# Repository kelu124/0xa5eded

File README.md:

# An 8-bit, 100Msps ADC standalone pHAT

aka 0xA5EDED == sha1(pHATrick)

# Description

An 8-bit, 125Msps ADC standalone pHAT

More? @TODO

# What

__Beware - these need to be updated with actual assembled board. v2 includes sees top going bottom and vice versa.__

# Acquisition of a square/sine wave

Signal coming out of a cheap DSO, should be around square, 4MHz

### Acquisition 

### Spectrum of a square wave at 125Msps

# Changes from v1

* Remove i2c to something simpler - MCP40D17T
* Let user choose offset or not
* Check OPAMP capa to get a 60MHz cutoff
* BAV / MD0100 to be removed
* Putting the rp2040 under the board, to expose the beautiful art to users

# License

This work is based a previous TAPR exploration, the [pic0rick project](https://github.com/kelu124/pic0rick/) - these open hardware and software, developped with open-source elements as much as possible.

Copyright Luc Jonveaux (kelu124@gmail.com) 2024

* The hardware is licensed under TAPR Open Hardware License (www.tapr.org/OHL)
* The software components are free software: you can redistribute it and/or modify it under the terms of the GNU General Public License as published by the Free Software Foundation, either version 3 of the License, or (at your option) any later version.
* The documentation is licensed under a [Creative Commons Attribution-ShareAlike 3.0 Unported License](http://creativecommons.org/licenses/by-sa/3.0/).

## Disclaimer

This project is distributed WITHOUT ANY EXPRESS OR IMPLIED WARRANTY, INCLUDING OF MERCHANTABILITY, SATISFACTORY QUALITY AND FITNESS FOR A PARTICULAR PURPOSE.

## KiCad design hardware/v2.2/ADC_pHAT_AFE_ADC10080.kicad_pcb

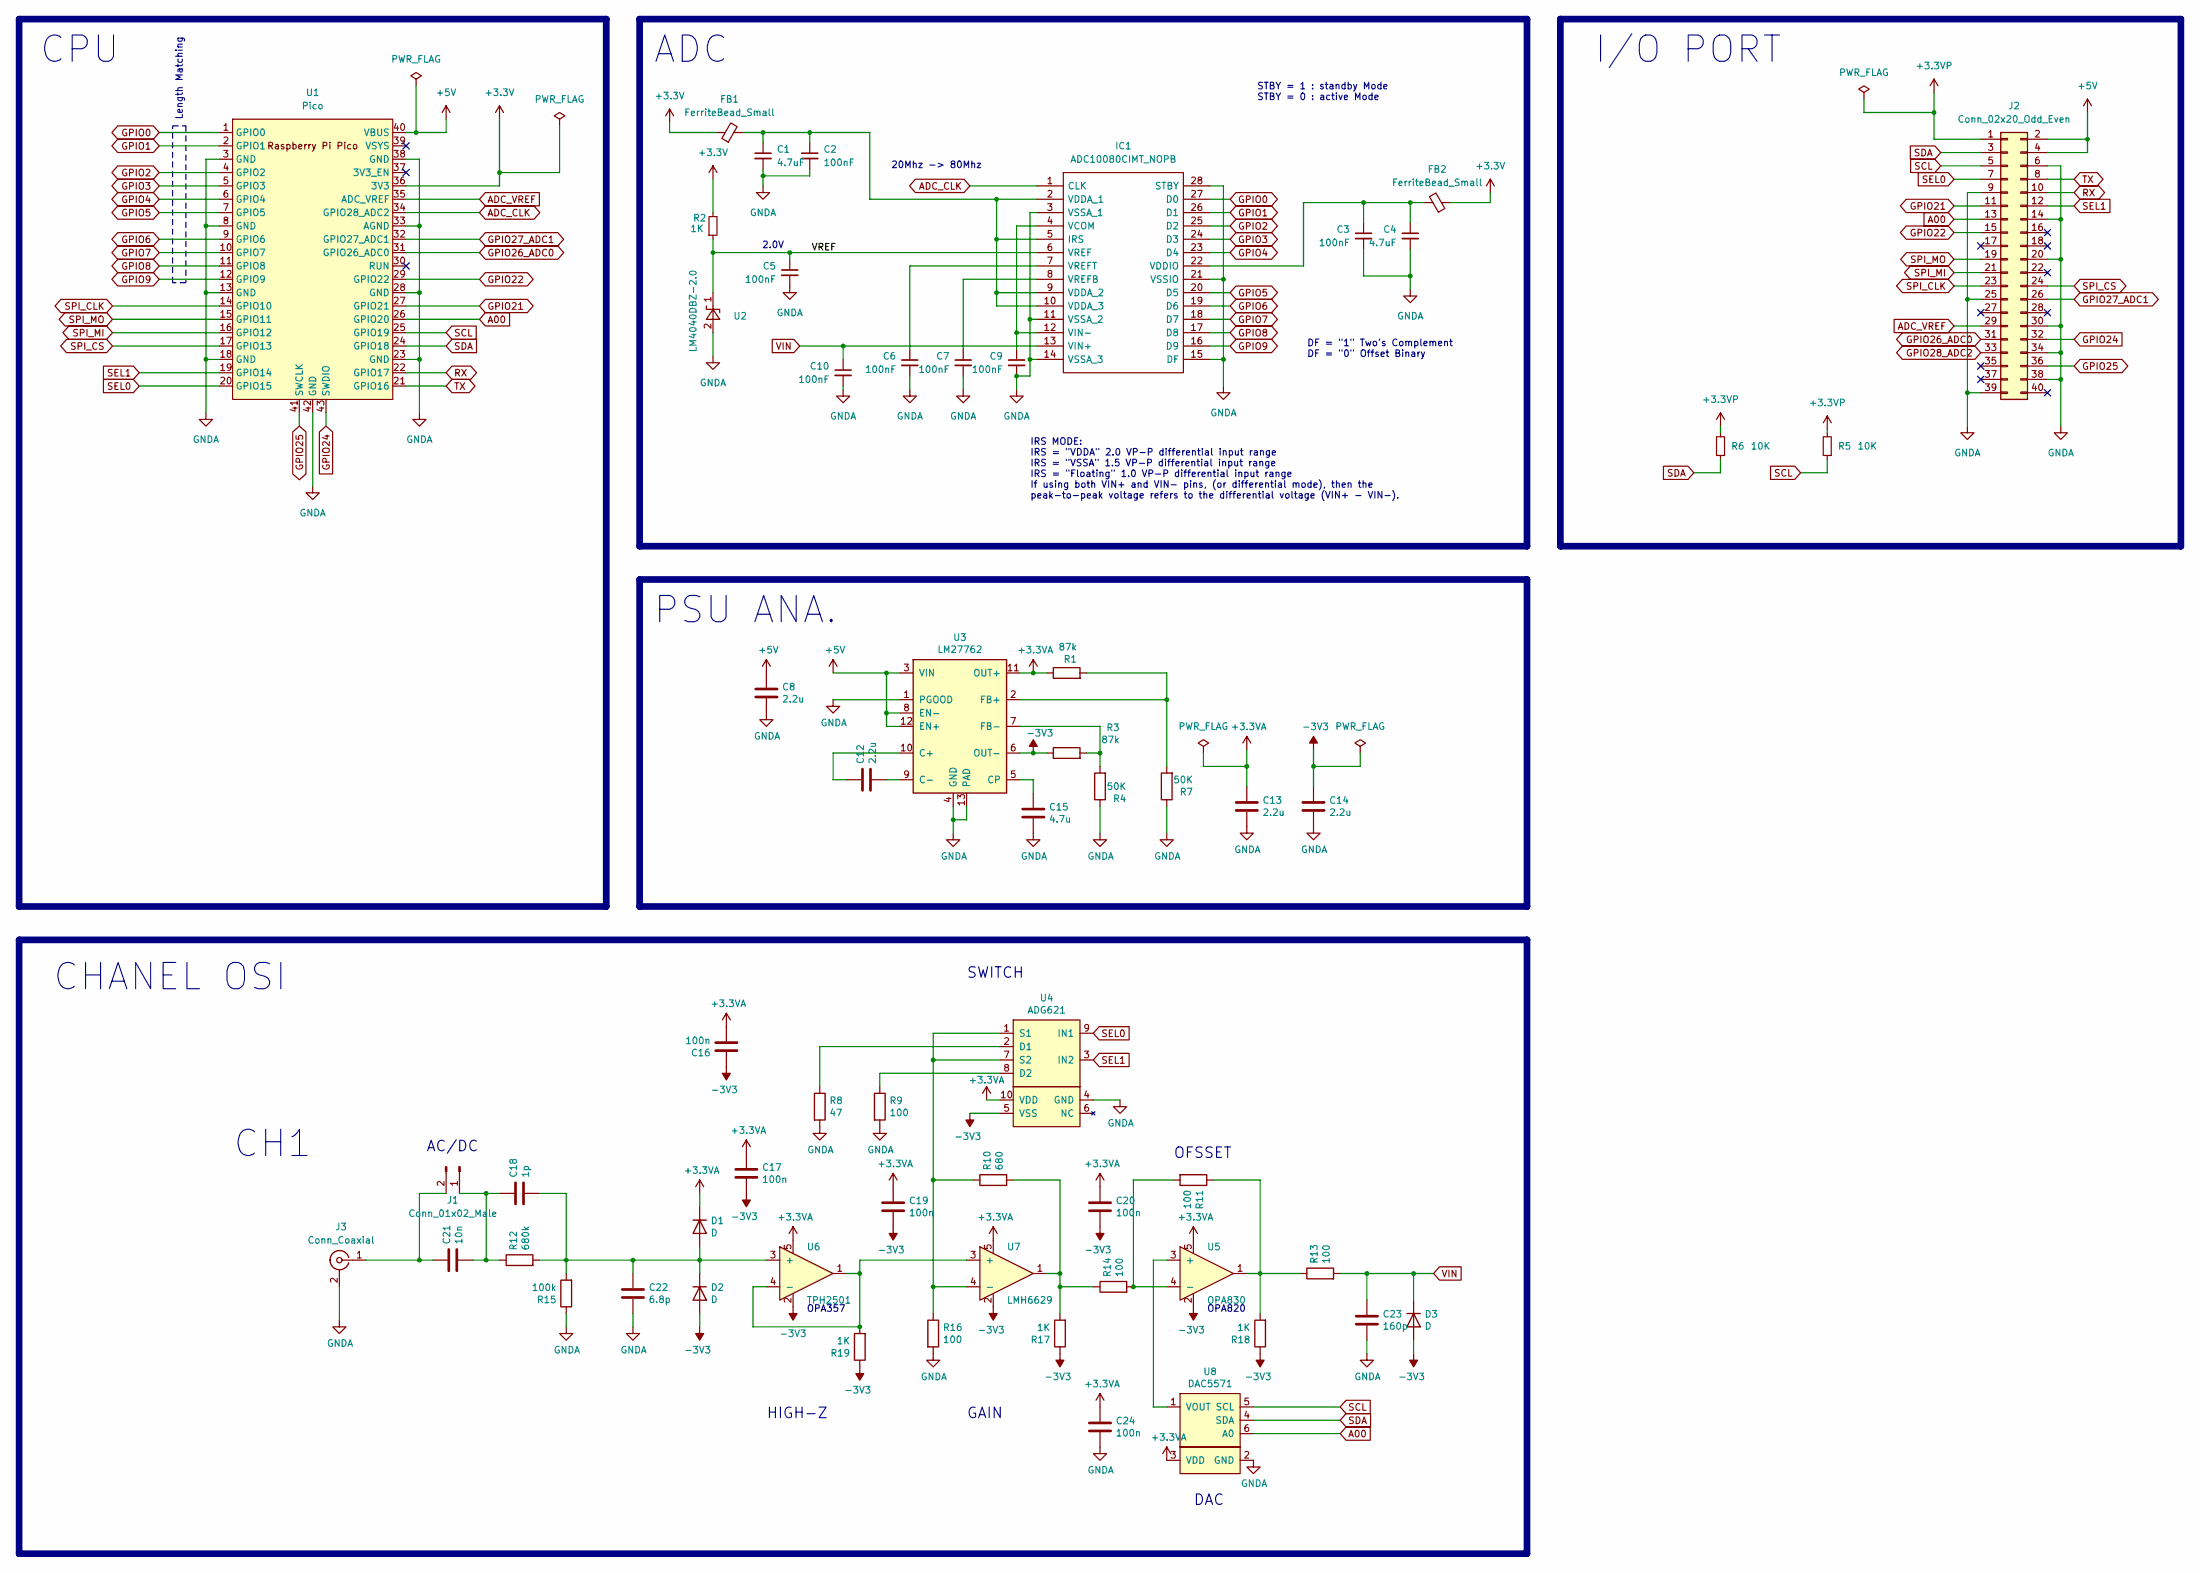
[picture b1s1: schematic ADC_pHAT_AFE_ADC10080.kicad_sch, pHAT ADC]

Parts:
C1, C4: 4.7uF; R_0603_1608Metric
C2, C3, C5, C6, C7, C9, C10: 100nF; R_0603_1608Metric
C8, C12, C13, C14: 2.2u; C_0603_1608Metric; MFR. Part # CL10A225KO8NNNC; LCSC Part # C23630
C15: 4.7u; C_0603_1608Metric; MFR. Part # CL10A475KO8NNNC; LCSC Part # C19666
C16, C17, C19, C20, C24: 100n; C_0603_1608Metric; MFR. Part # CC0603KRX7R9BB104; LCSC Part # C14663
C18: 1p; C_0603_1608Metric; MFR. Part # CL10C010CB8NNNC; LCSC Part # C23969
C21: 10n; C_0603_1608Metric; MFR. Part # 0603B103K500NT; LCSC Part # C57112
C22: 6.8p; C_0603_1608Metric; MFR. Part # 0603CG6R8C500NT; LCSC Part # C1679
C23: 160p; C_0603_1608Metric; MFR. Part # FN18X104K160PSG; LCSC Part # C235729
D1, D2, D3: D; D_0603_1608Metric
FB1, FB2: FerriteBead_Small; L_1206_3216Metric
IC1: ADC10080CIMT_NOPB; SOP65P640X120-28N; Mouser Part Number 926-ADC10080CIMTNOPB
J1: Conn_01x02_Male; PinHeader_1x02_P1.00mm_Vertical_SMD_Pin1Left
J2: Conn_02x20_Odd_Even; PinSocket_2x20_P2.54mm_Vertical
J3: Conn_Coaxial; AMPHENOL_132357-11-MOD
R1, R3: 87k; R_0603_1608Metric; MFR. Part # 0603WAF8202T5E; LCSC Part # C23254
R2: 1K; R_0603_1608Metric
R4, R7: 50K; R_0603_1608Metric; MFR. Part # 0603WAF1503T5E; LCSC Part # C22807
R5, R6: 10K; R_0603_1608Metric
R8: 47; R_1206_3216Metric; MFR. Part # 0603WAF470JT5E; LCSC Part # C23182
R9, R16: 100; R_1206_3216Metric; MFR. Part # 0603WAF1000T5E; LCSC Part # C22775
R10: 680; R_0603_1608Metric; MFR. Part # 0603WAF6801T5E; LCSC Part # C23212
R11, R13, R14: 100; R_0603_1608Metric; MFR. Part # 0603WAF1000T5E; LCSC Part # C22775
R12: 680k; R_0603_1608Metric; MFR. Part # 0603WAF6803T5E; LCSC Part # C25822
R15: 100k; R_0603_1608Metric; MFR. Part # 0603WAF1003T5E; LCSC Part # C25803
R17, R18, R19: 1K; R_0603_1608Metric; MFR. Part # 0603WAF1001T5E; LCSC Part # C21190
U1: Pico; RPi_Pico_SMD
U2: LM4040DBZ-2.0; SOT-23
U3: LM27762; WSON-12-1EP_3x2mm_P0.5mm_EP1x2.65_ThermalVias; MFR. Part # LM27762DSSR; LCSC Part # C473398
U4: ADG621; MSOP-10_3x3mm_P0.5mm; LCSC Part # C208597
U5: OPA830; SOT-23-5; LCSC Part # C181539
U6: TPH2501; SOT-23-5; LCSC Part # C139385
U7: LMH6629; SOT-23-5; LCSC Part # C206003
U8: DAC5571; SOT-23-6; LCSC Part # C24061

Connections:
+3.3V: FB1.1, FB2.1, R2.2, U1.36 (3V3)
+3.3VA: C13.1, C16.2, C17.1, C19.1, C20.1, C24.1, D1.1 (K), R1.1, U3.11 (OUT+), U4.10 (VDD), U5.5, U6.5, U7.5, U8.3 (VDD)
+3.3VP: J2.1, R5.2, R6.2
+5V: C8.1, J2.2, J2.4, U1.40 (VBUS), U3.3 (VIN), U3.8 (EN-), U3.12 (EN+)
-3V3: C14.1, C16.1, C17.2, C19.2, C20.2, D2.2 (A), D3.2 (A), R3.1, R17.1, R18.1, R19.1, U3.6 (OUT-), U4.5 (VSS), U5.2, U6.2, U7.2
/VREF: C5.1, IC1.6 (VREF), R2.1, U2.1 (K)
A00: J2.13, U1.26 (GPIO20), U8.6 (A0)
ADC_CLK: IC1.1 (CLK), U1.34 (GPIO28_ADC2)
ADC_VREF: J2.29, U1.35 (ADC_VREF)
GNDA: C1.2, C2.2, C3.2, C4.2, C5.2, C6.2, C7.2, C8.2, C9.2, C10.2, C13.2, C14.2, C15.2, C22.2, C23.2, C24.2, IC1.3 (VSSA_1), IC1.11 (VSSA_2), IC1.14 (VSSA_3), IC1.15 (DF), IC1.21 (VSSIO), IC1.28 (STBY), J2.6, J2.9, J2.14, J2.20, J2.25, J2.30, J2.34, J2.38, J2.39, J3.2 (Ext), R4.1, R7.1, R8.2, R9.2, R15.1, R16.2, U1.3 (GND), U1.8 (GND), U1.13 (GND), U1.18 (GND), U1.23 (GND), U1.28 (GND), U1.33 (AGND), U1.38 (GND), U1.42 (GND), U2.2 (A), U3.1 (PGOOD), U3.4 (GND), U3.13 (PAD), U4.4 (GND), U8.2 (GND)
GPIO0: IC1.27 (D0), U1.1 (GPIO0)
GPIO1: IC1.26 (D1), U1.2 (GPIO1)
GPIO2: IC1.25 (D2), U1.4 (GPIO2)
GPIO3: IC1.24 (D3), U1.5 (GPIO3)
GPIO4: IC1.23 (D4), U1.6 (GPIO4)
GPIO5: IC1.20 (D5), U1.7 (GPIO5)
GPIO6: IC1.19 (D6), U1.9 (GPIO6)
GPIO7: IC1.18 (D7), U1.10 (GPIO7)
GPIO8: IC1.17 (D8), U1.11 (GPIO8)
GPIO9: IC1.16 (D9), U1.12 (GPIO9)
GPIO21: J2.11, U1.27 (GPIO21)
GPIO22: J2.15, U1.29 (GPIO22)
GPIO24: J2.32, U1.43 (SWDIO)
GPIO25: J2.36, U1.41 (SWCLK)
GPIO26_ADC0: J2.31, U1.31 (GPIO26_ADC0)
GPIO27_ADC1: J2.26, U1.32 (GPIO27_ADC1)
GPIO28_ADC2: J2.33
unnamed: C18.2, C22.1, D1.2 (A), D2.1 (K), R12.2, R15.2, U6.3 (+)
unnamed: C1.1, C2.1, FB1.2, IC1.2 (VDDA_1), IC1.5 (IRS), IC1.9 (VDDA_2), IC1.10 (VDDA_3)
unnamed: C9.1, IC1.4 (VCOM), IC1.12 (VIN-)
unnamed: C3.1, C4.1, FB2.2, IC1.22 (VDDIO)
unnamed: C7.1, IC1.8 (VREFB)
unnamed: C6.1, IC1.7 (VREFT)
unnamed: C18.1, C21.2, J1.1, R12.1
unnamed: C21.1, J1.2, J3.1 (In)
unnamed: R10.2, R14.1, R17.2, U7.1
unnamed: R11.1, R13.1, R18.2, U5.1
unnamed: C12.1, U3.10 (C+)
unnamed: C12.2, U3.9 (C-)
unnamed: C15.1, U3.5 (CP)
unnamed: R1.2, R7.2, U3.2 (FB+)
unnamed: R3.2, R4.2, U3.7 (FB-)
unnamed: R8.1, U4.2 (D1)
unnamed: R9.1, U4.8 (D2)
unnamed: R10.1, R16.1, U4.1 (S1), U4.7 (S2), U7.4 (-)
unnamed: U5.3 (+), U8.1 (VOUT)
unnamed: R11.2, R14.2, U5.4 (-)
unnamed: R19.2, U6.1, U6.4 (-), U7.3 (+)
RX: J2.10, U1.22 (GPIO17)
SCL: J2.5, R5.1, U1.25 (GPIO19), U8.5 (SCL)
SDA: J2.3, R6.1, U1.24 (GPIO18), U8.4 (SDA)
SEL0: J2.7, U1.20 (GPIO15), U4.9 (IN1)
SEL1: J2.12, U1.19 (GPIO14), U4.3 (IN2)
SPI_CLK: J2.23, U1.14 (GPIO10)
SPI_CS: J2.24, U1.17 (GPIO13)
SPI_MI: J2.21, U1.16 (GPIO12)
SPI_MO: J2.19, U1.15 (GPIO11)
TX: J2.8, U1.21 (GPIO16)
VIN: C10.1, C23.1, D3.1 (K), IC1.13 (VIN+), R13.2

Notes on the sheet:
CHANEL OSI
IRS MODE: IRS = "VDDA" 2.0 VP-P differential input range IRS = "VSSA" 1.5 VP-P differential input range IRS = "Floating" 1.0 VP-P differential input range If using both VIN+ and VIN- pins, (or differential mode), then the peak-to-peak voltage refers to the differential voltage (VIN+ - VIN-).
AC/DC
DAC
CPU
OPA820
PSU ANA.
I/O PORT
GAIN
STBY = 1 : standby Mode STBY = 0 : active Mode
20Mhz -> 80Mhz
ADC
2.0V
OPA357
Length Matching
SWITCH
DF = "1" Two's Complement DF = "0" Offset Binary
HIGH-Z
OFSSET
CH1

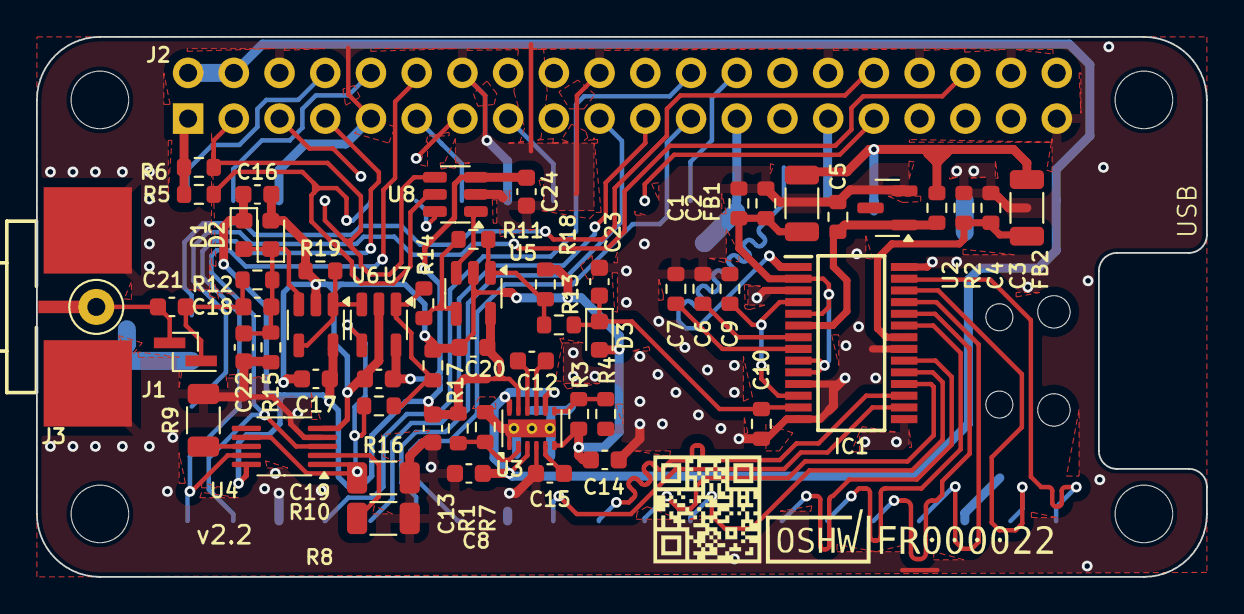
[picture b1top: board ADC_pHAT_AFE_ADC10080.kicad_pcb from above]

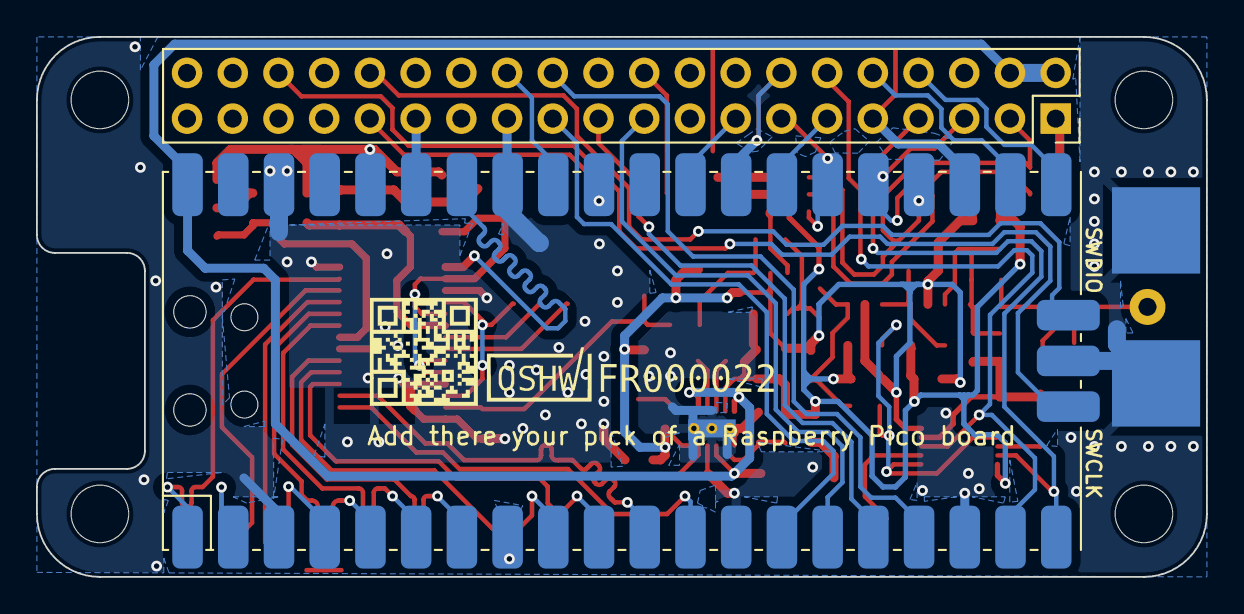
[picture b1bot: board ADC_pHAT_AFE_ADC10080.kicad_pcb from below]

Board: 2 copper layers, 65.0 x 30.0 mm, 59 parts (2 on the bottom side), 58 nets.

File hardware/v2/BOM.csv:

"Reference","Value","Datasheet","Footprint","Qty","DNP"
"C1,C3,C4","22uF","~","Capacitor_SMD:C_0603_1608Metric","3",""
"C2,C5,C6,C7,C11","100nF","~","Capacitor_SMD:C_0603_1608Metric","5",""
"C8,C12,C13,C14","2.2u","https://datasheet.lcsc.com/lcsc/1810271109_Samsung-Electro-M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","Capacitor_SMD:C_0603_1608Metric","4",""
"C9,C16,C17,C19,C20,C24,C25","100n","https://datasheet.lcsc.com/lcsc/1809301912_YAGEO-CC0603KRX7R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","Capacitor_SMD:C_0603_1608Metric","7",""
"C10","1u","https://datasheet.lcsc.com/lcsc/1810261812_Samsung-Electro-M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","Capacitor_SMD:C_0603_1608Metric","1",""
"C15","4.7u","https://datasheet.lcsc.com/lcsc/1810261514_Samsung-Electro-M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","Capacitor_SMD:C_0603_1608Metric","1",""
"C18","1p","https://datasheet.lcsc.com/lcsc/1810261512_Samsung-Electro-M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","Capacitor_SMD:C_0603_1608Metric","1",""
"C21","10n","https://datasheet.lcsc.com/lcsc/2102081402_FH-Guangdong-Feng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","Capacitor_SMD:C_0603_1608Metric","1",""
"C22","6.8p","https://datasheet.lcsc.com/lcsc/1811061822_FH-Guangdong-Feng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","Capacitor_SMD:C_0603_1608Metric","1",""
"C23","160p","https://datasheet.lcsc.com/lcsc/1811101032_PSA-Prosperity-Di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","Capacitor_SMD:C_0603_1608Metric","1",""
"D1,D2,D3","D","~","Diode_SMD:D_0603_1608Metric","3",""
"FB1,FB2","FerriteBead_Small","~","Resistor_SMD:R_0603_1608Metric","2",""
"J1","Conn_01x02_Male","~","Connector_PinHeader_1.00mm:PinHeader_1x02_P1.00mm_Vertical_SMD_Pin1Left","1",""
"J2","Conn_02x20_Odd_Even","~","Connector_PinSocket_2.54mm:PinSocket_2x20_P2.54mm_Vertical","1",""
"J3","Conn_Coaxial","~","ICTAMKY_V8:AMPHENOL_132357-11-MOD","1",""
"R1,R3","87k","https://datasheet.lcsc.com/lcsc/1811081712_UNI-ROYAL-Uniroya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","Resistor_SMD:R_0603_1608Metric","2",""
"R2","10K","~","Resistor_SMD:R_0603_1608Metric","1",""
"R4,R7","50k","https://datasheet.lcsc.com/lcsc/1811021211_UNI-ROYAL-Uniroya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","Resistor_SMD:R_0603_1608Metric","2",""
"R5,R17,R18,R19","1k","https://datasheet.lcsc.com/lcsc/1811141223_UNI-ROYAL-Uniroya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","Resistor_SMD:R_0603_1608Metric","4",""
"R8","47","https://datasheet.lcsc.com/lcsc/1811101920_UNI-ROYAL-Uniroya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","Resistor_SMD:R_0603_1608Metric","1",""
"R9,R11,R13,R14,R16","100","https://datasheet.lcsc.com/lcsc/1811081710_UNI-ROYAL-Uniroya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","Resistor_SMD:R_0603_1608Metric","5",""
"R10","680","https://datasheet.lcsc.com/lcsc/1811081710_UNI-ROYAL-Uniroya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","Resistor_SMD:R_0603_1608Metric","1",""
"R12","680k","https://datasheet.lcsc.com/lcsc/1811081723_UNI-ROYAL-Uniroya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","Resistor_SMD:R_0603_1608Metric","1",""
"R15","100k","https://datasheet.lcsc.com/lcsc/1810201809_UNI-ROYAL-Uniroya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","Resistor_SMD:R_0603_1608Metric","1",""
"U1","Pico","","ICTAMKY_V8:RPi_Pico_SMD","1",""
"U2","ADC08100CIMTCX/NOPB(TSSOP-24)","","Package_SO:TSSOP-24_4.4x7.8mm_P0.65mm","1",""
"U3","LM27762","https://datasheet.lcsc.com/lcsc/2001031722_Texas-Instruments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","Package_SON:WSON-12-1EP_3x2mm_P0.5mm_EP1x2.65_ThermalVias","1",""
"U4","ADG621","","Package_SO:MSOP-10_3x3mm_P0.5mm","1",""
"U5","OPA830","","Package_TO_SOT_SMD:SOT-23-5","1",""
"U6","TPH2501","","Package_TO_SOT_SMD:SOT-23-5","1",""
"U7","LMH6629","","Package_TO_SOT_SMD:SOT-23-5","1",""
"U8","DAC5571","","Package_TO_SOT_SMD:SOT-23-6","1",""
"U9","TLV271","","Package_TO_SOT_SMD:SOT-23-5","1",""
"U10","LM4040DBZ-2.0","https://datasheet.lcsc.com/lcsc/1809111512_Texas-Instruments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","Package_TO_SOT_SMD:SOT-23","1",""

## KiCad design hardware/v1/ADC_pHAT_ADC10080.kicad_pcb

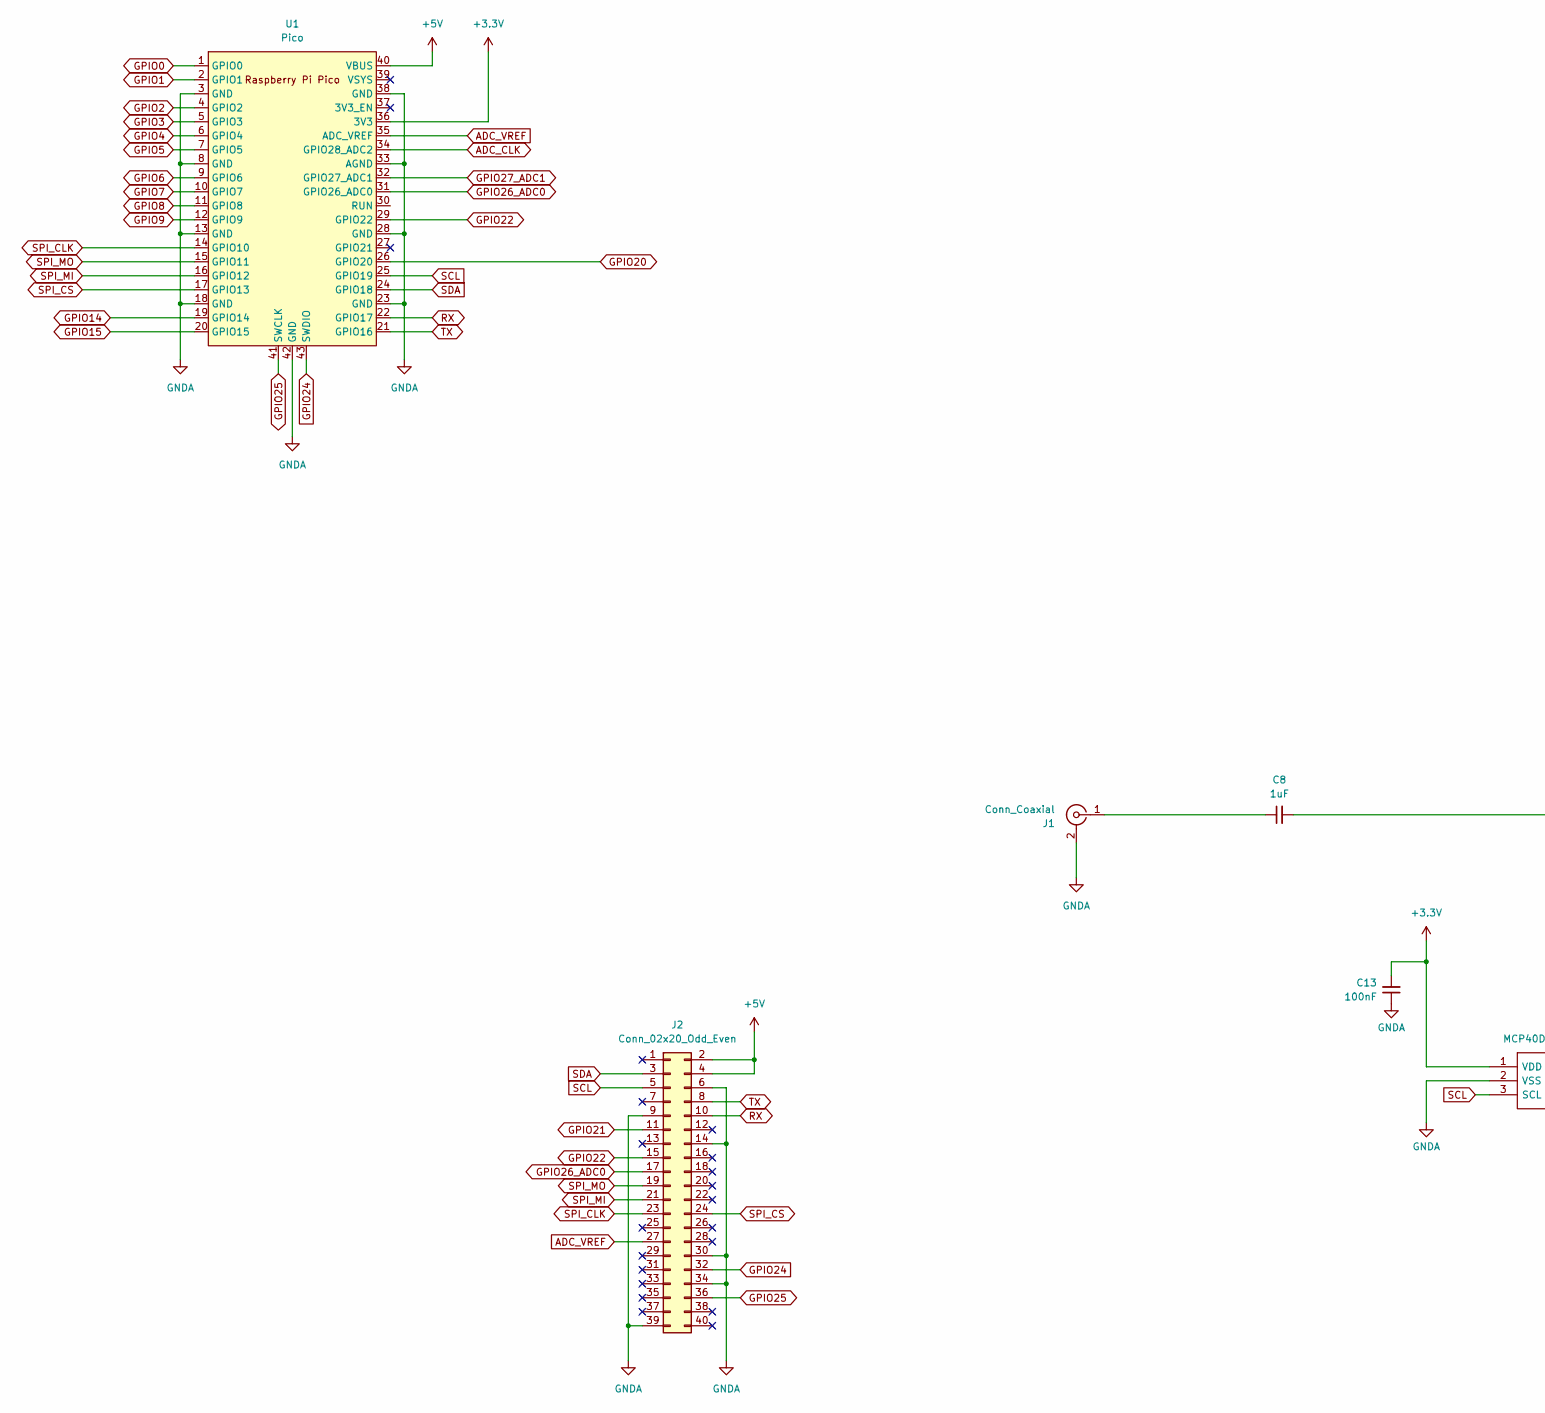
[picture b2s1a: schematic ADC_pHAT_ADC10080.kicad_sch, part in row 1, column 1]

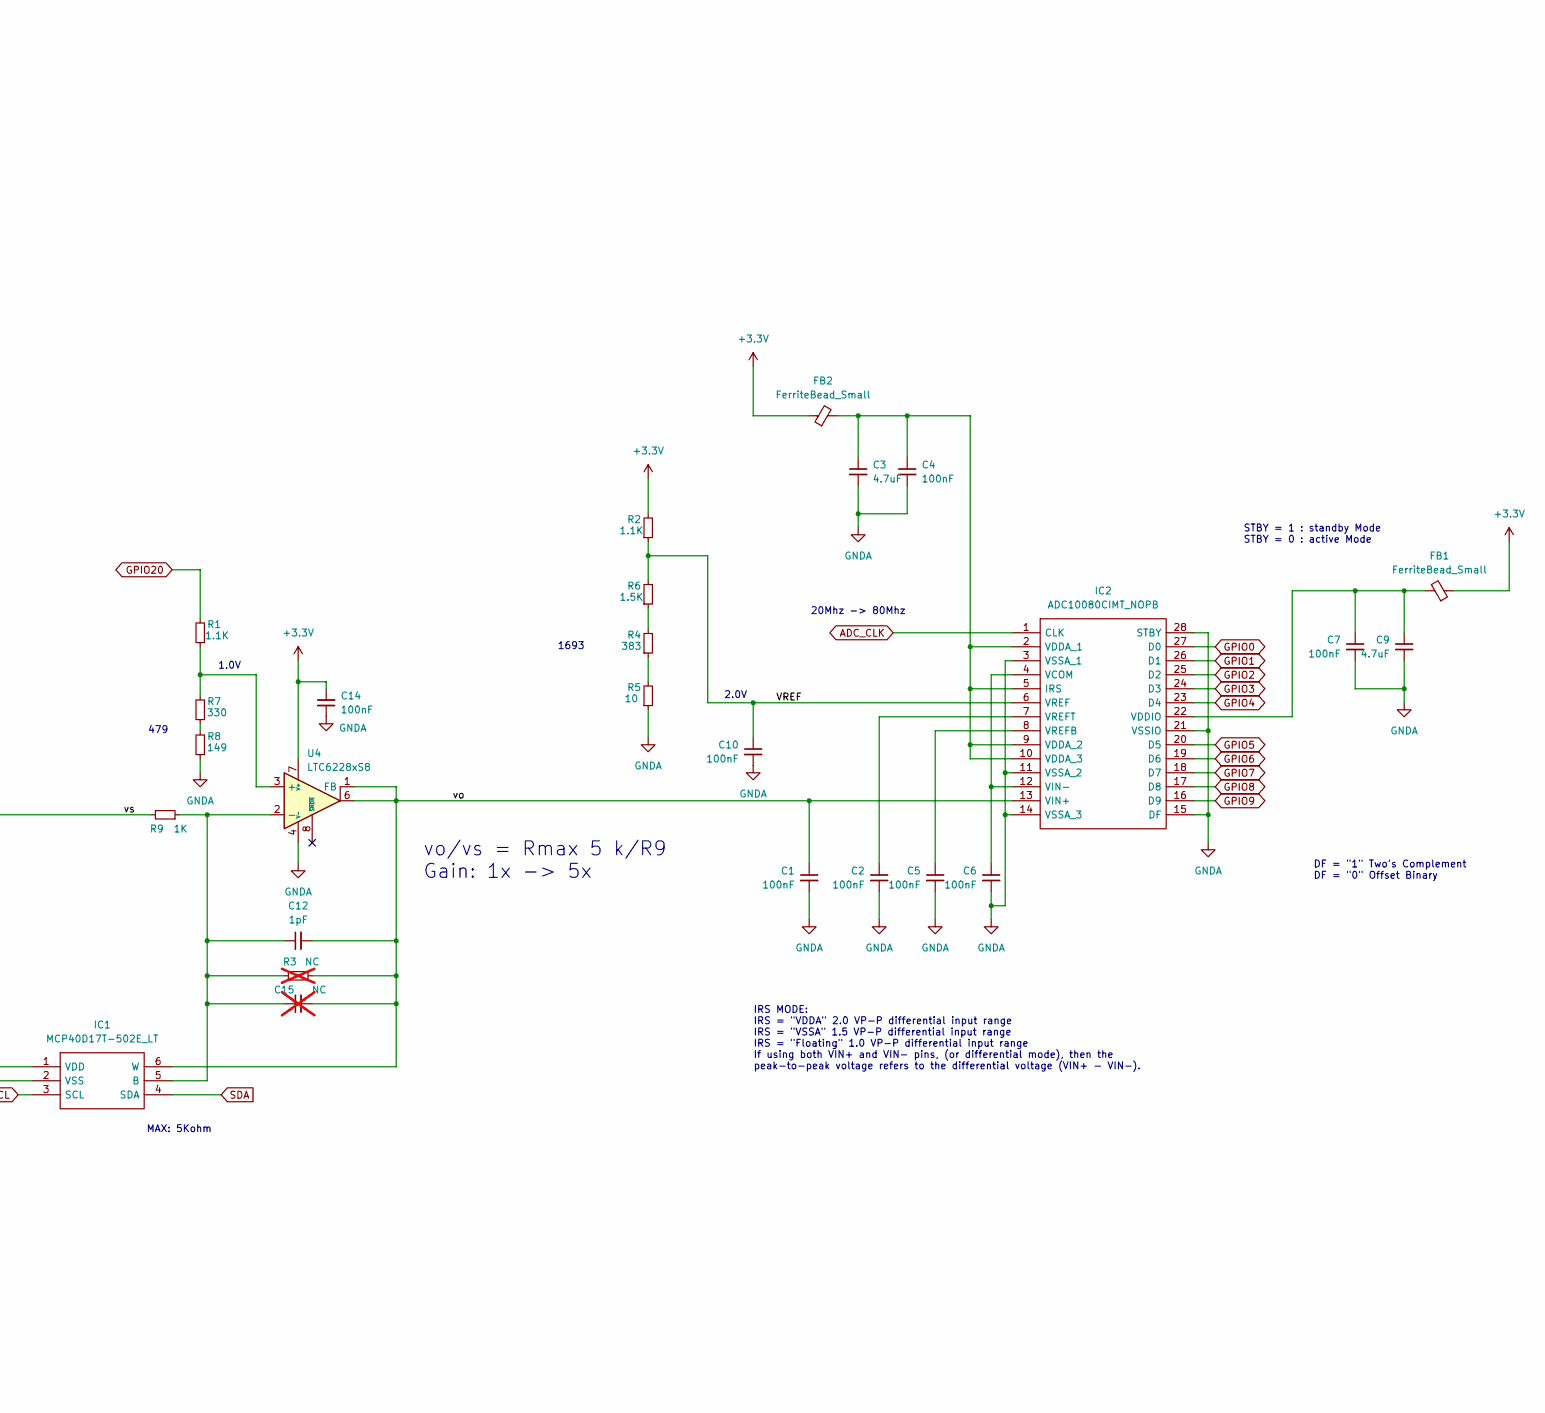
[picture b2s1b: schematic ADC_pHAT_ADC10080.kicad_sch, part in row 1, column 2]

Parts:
C1, C2, C4, C5, C6, C7, C10, C13, C14: 100nF; C_1206_3216Metric
C3, C9: 4.7uF; C_1206_3216Metric
C8: 1uF; C_1206_3216Metric
C12: 1pF; C_1206_3216Metric
C15: NC; C_1206_3216Metric; not fitted
FB1, FB2: FerriteBead_Small; L_1206_3216Metric
IC1: MCP40D17T-502E_LT; SOT65P210X110-6N; Mouser Part Number 579-MCP40D17T502E/LT
IC2: ADC10080CIMT_NOPB; SOP65P640X120-28N; Mouser Part Number 926-ADC10080CIMTNOPB
J1: Conn_Coaxial; AMPHENOL_132357-11
J2: Conn_02x20_Odd_Even; PinSocket_2x20_P2.54mm_Vertical
R1, R2: 1.1K; R_1206_3216Metric
R3: NC; R_1206_3216Metric; not fitted
R4: 383; R_1206_3216Metric
R5: 10; R_1206_3216Metric
R6: 1.5K; R_1206_3216Metric
R7: 330; R_1206_3216Metric
R8: 149; R_1206_3216Metric
R9: 1K; R_1206_3216Metric
U1: Pico; RPi_Pico_SMD
U4: LTC6228xS8; SO-8_3.9x4.9mm_P1.27mm

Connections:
+3.3V: C13.2, C14.2, FB1.1, FB2.1, IC1.1 (VDD), R2.2, U1.36 (3V3), U4.7 (V+)
+5V: J2.2, J2.4, U1.40 (VBUS)
/VREF: C10.1, IC2.6 (VREF), R2.1, R6.2
/vo: C1.1, C12.2, C15.2, IC1.6 (W), IC2.13 (VIN+), R3.1, U4.1 (FB), U4.6
/vs: C8.2, R9.2
ADC_CLK: IC2.1 (CLK), U1.34 (GPIO28_ADC2)
ADC_VREF: J2.27, U1.35 (ADC_VREF)
GNDA: C1.2, C2.2, C3.2, C4.2, C5.2, C6.2, C7.2, C9.2, C10.2, C13.1, C14.1, IC1.2 (VSS), IC2.3 (VSSA_1), IC2.11 (VSSA_2), IC2.14 (VSSA_3), IC2.15 (DF), IC2.21 (VSSIO), IC2.28 (STBY), J1.2 (Ext), J2.6, J2.9, J2.14, J2.30, J2.34, J2.39, R5.1, R8.1, U1.3 (GND), U1.8 (GND), U1.13 (GND), U1.18 (GND), U1.23 (GND), U1.28 (GND), U1.33 (AGND), U1.38 (GND), U1.42 (GND), U4.4 (V-), U4.5 (V-)
GPIO0: IC2.27 (D0), U1.1 (GPIO0)
GPIO1: IC2.26 (D1), U1.2 (GPIO1)
GPIO2: IC2.25 (D2), U1.4 (GPIO2)
GPIO3: IC2.24 (D3), U1.5 (GPIO3)
GPIO4: IC2.23 (D4), U1.6 (GPIO4)
GPIO5: IC2.20 (D5), U1.7 (GPIO5)
GPIO6: IC2.19 (D6), U1.9 (GPIO6)
GPIO7: IC2.18 (D7), U1.10 (GPIO7)
GPIO8: IC2.17 (D8), U1.11 (GPIO8)
GPIO9: IC2.16 (D9), U1.12 (GPIO9)
GPIO14: U1.19 (GPIO14)
GPIO15: U1.20 (GPIO15)
GPIO20: R1.2, U1.26 (GPIO20)
GPIO21: J2.11
GPIO22: J2.15, U1.29 (GPIO22)
GPIO24: J2.32, U1.43 (SWDIO)
GPIO25: J2.36, U1.41 (SWCLK)
GPIO26_ADC0: J2.17, U1.31 (GPIO26_ADC0)
GPIO27_ADC1: U1.32 (GPIO27_ADC1)
unnamed: C12.1, C15.1, IC1.5 (B), R3.2, R9.1, U4.2 (-)
unnamed: C3.1, C4.1, FB2.2, IC2.2 (VDDA_1), IC2.5 (IRS), IC2.9 (VDDA_2), IC2.10 (VDDA_3)
unnamed: C6.1, IC2.4 (VCOM), IC2.12 (VIN-)
unnamed: C7.1, C9.1, FB1.2, IC2.22 (VDDIO)
unnamed: C5.1, IC2.8 (VREFB)
unnamed: C2.1, IC2.7 (VREFT)
unnamed: C8.1, J1.1 (In)
unnamed: R4.1, R5.2
unnamed: R4.2, R6.1
unnamed: R7.1, R8.2
unnamed: R1.1, R7.2, U4.3 (+)
RX: J2.10, U1.22 (GPIO17)
SCL: IC1.3 (SCL), J2.5, U1.25 (GPIO19)
SDA: IC1.4 (SDA), J2.3, U1.24 (GPIO18)
SPI_CLK: J2.23, U1.14 (GPIO10)
SPI_CS: J2.24, U1.17 (GPIO13)
SPI_MI: J2.21, U1.16 (GPIO12)
SPI_MO: J2.19, U1.15 (GPIO11)
TX: J2.8, U1.21 (GPIO16)

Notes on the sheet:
STBY = 1 : standby Mode STBY = 0 : active Mode
DF = "1" Two's Complement DF = "0" Offset Binary
1693
479
20Mhz -> 80Mhz
MAX: 5Kohm
IRS MODE: IRS = "VDDA" 2.0 VP-P differential input range IRS = "VSSA" 1.5 VP-P differential input range IRS = "Floating" 1.0 VP-P differential input range If using both VIN+ and VIN- pins, (or differential mode), then the peak-to-peak voltage refers to the differential voltage (VIN+ - VIN-).
vo/vs = Rmax 5 k/R9 Gain: 1x -> 5x
2.0V
1.0V

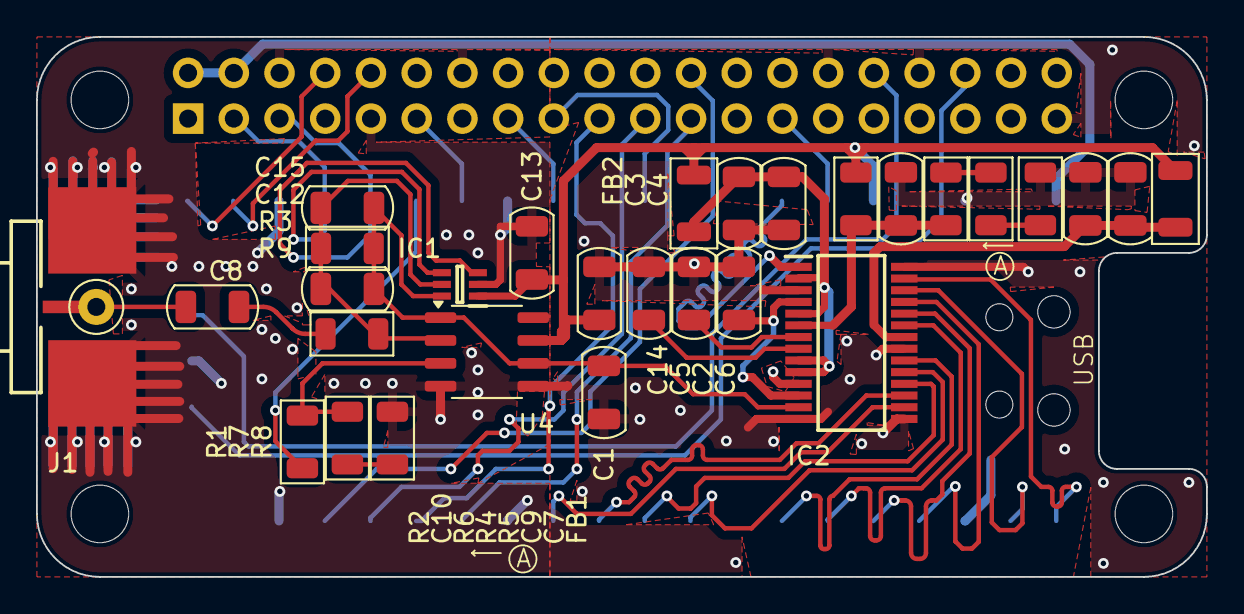
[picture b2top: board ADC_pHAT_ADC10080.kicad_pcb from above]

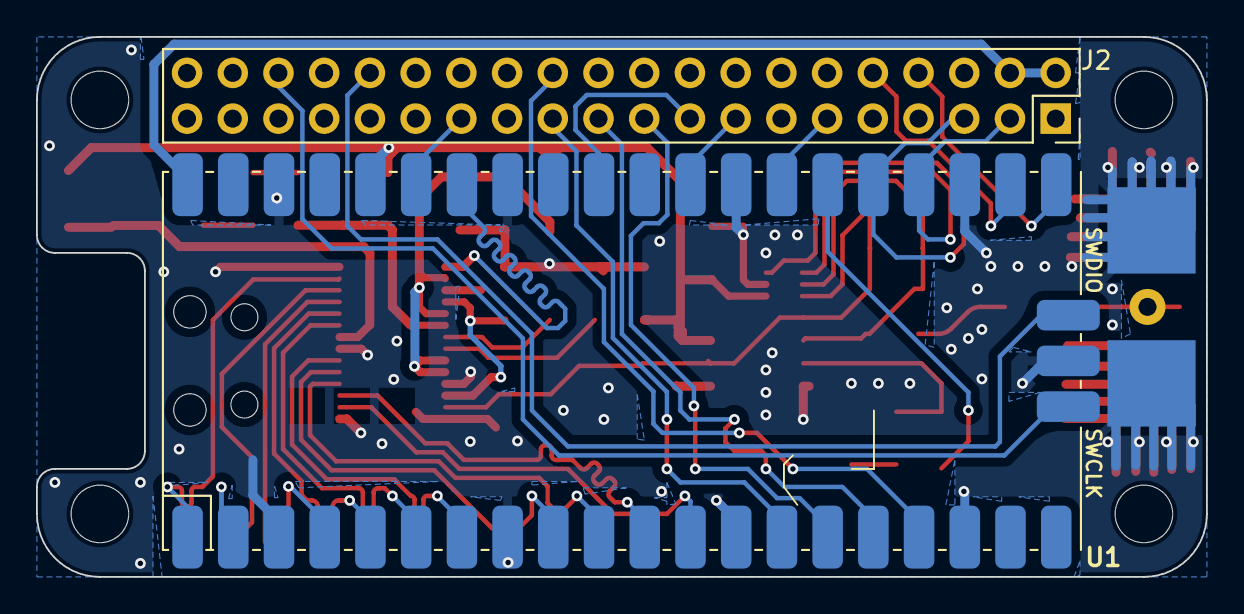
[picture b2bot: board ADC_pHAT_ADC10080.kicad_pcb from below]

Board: 2 copper layers, 65.0 x 30.0 mm, 31 parts (2 on the bottom side), 42 nets.

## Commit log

2024-04-06 First release of the pHAT
2024-05-16 autoupdate
2024-09-26 Test with DAC2932
2024-11-06 Adding v2.1 piece
2024-12-01 v2.2 updates
